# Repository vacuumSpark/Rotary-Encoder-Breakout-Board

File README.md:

# Rotary-Encoder-Breakout-Board
Small PCB breakout featuring a rotary encoder with push switch. This board also featured debounce filtering and LED feedback.

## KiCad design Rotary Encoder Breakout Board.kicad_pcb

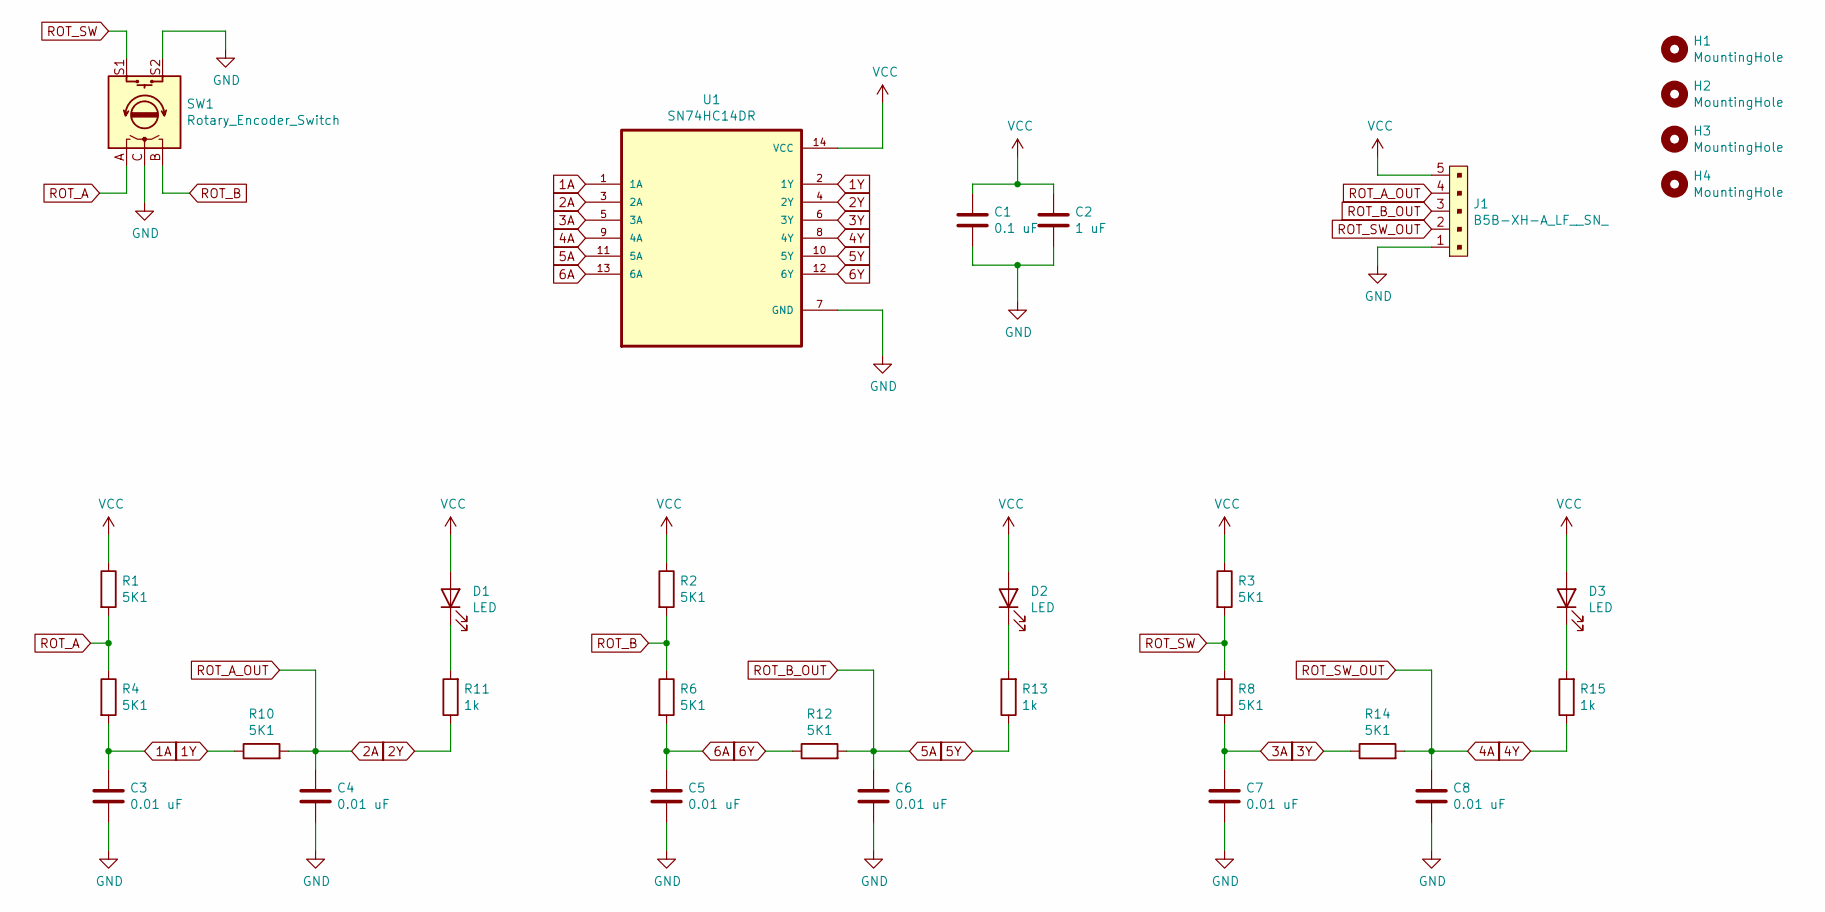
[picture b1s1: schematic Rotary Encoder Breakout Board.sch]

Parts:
C1: 0.1 uF; C_0805_2012Metric
C2: 1 uF; C_0805_2012Metric
C3, C4, C5, C6, C7, C8: 0.01 uF; C_0805_2012Metric
D1, D2, D3: LED; LED_1206_3216Metric
H1, H2, H3, H4: MountingHole; MountingHole_4.3mm_M4_ISO7380
J1: B5B-XH-A_LF__SN_; PinHeader_1x05_P2.54mm_Vertical; MPN B5B-XH-A(LF)(SN); Digi-Key_PN 455-2270-ND
R1, R2, R3, R4, R6, R8, R10, R12, R14: 5K1; R_0805_2012Metric
R11, R13, R15: 1k; R_0805_2012Metric
SW1: Rotary_Encoder_Switch; RotaryEncoder_Alps_EC11E-Switch_Vertical_H20mm
U1: SN74HC14DR; SOIC-14_3.9x8.7mm_P1.27mm

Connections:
1A: C3.1, R4.2, U1.1 (1A)
1Y: R10.1, U1.2 (1Y)
2A: C4.1, J1.4, R10.2, U1.3 (2A)
2Y: R11.1, U1.4 (2Y)
3A: C7.1, R8.2, U1.5 (3A)
3Y: R14.1, U1.6 (3Y)
4A: C8.1, J1.2, R14.2, U1.9 (4A)
4Y: R15.1, U1.8 (4Y)
5A: C6.1, J1.3, R12.2, U1.11 (5A)
5Y: R13.1, U1.10 (5Y)
6A: C5.1, R6.2, U1.13 (6A)
6Y: R12.1, U1.12 (6Y)
GND: C1.2, C2.2, C3.2, C4.2, C5.2, C6.2, C7.2, C8.2, J1.1, SW1.C, SW1.S2, U1.7 (GND)
unnamed: D1.1 (K), R11.2
unnamed: D2.1 (K), R13.2
unnamed: D3.1 (K), R15.2
ROT_A: R1.2, R4.1, SW1.A
ROT_B: R2.2, R6.1, SW1.B
ROT_SW: R3.2, R8.1, SW1.S1
VCC: C1.1, C2.1, D1.2 (A), D2.2 (A), D3.2 (A), J1.5, R1.1, R2.1, R3.1, U1.14 (VCC)

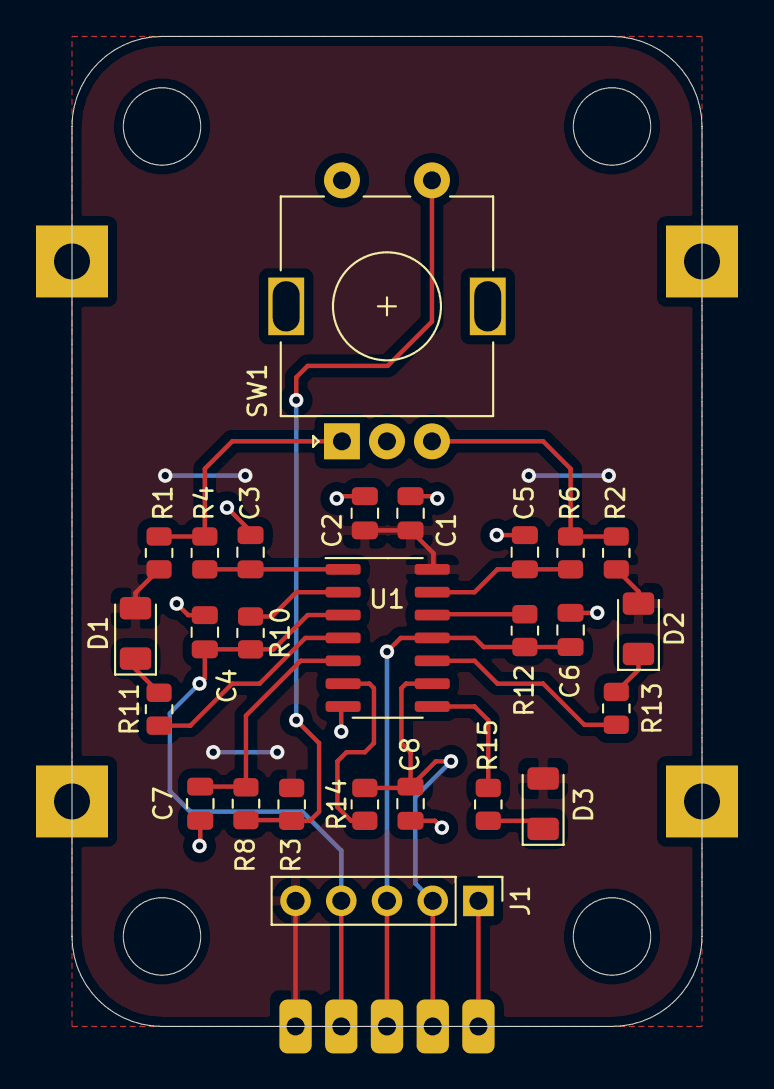
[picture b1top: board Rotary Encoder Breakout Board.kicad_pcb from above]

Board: 2 copper layers, 35.0 x 55.0 mm, 30 parts (0 on the bottom side), 20 nets.

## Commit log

2020-12-27 initial schematic and board layout
2020-12-28 simplified schematic + updated pcb + added pours, outline and mounting holes
2020-12-28 work in progress
2021-02-06 changed led footprint + added cast. holes + placed labels + pin header
2021-02-06 added OSHW maker + designed with KiCAd + fiducials + license
2021-02-06 added directories
